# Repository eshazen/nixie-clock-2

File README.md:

# nixie-clock-2
Simple nixie clock based on ATMega861 microcontroller

<table>
  <tr>
    <td width=50%>
    <td>
</table>

```hardware/DriverBoard```

ExpressPCB layout for MCU/Driver board with ATTiny861A driving 4 IN-2B nixies.

```hardware/nixie_socket```

KiCAD design for a two-digit nixie mounting/breakout board

```software/clock```

C code for ATTiny861A to drive the clock display

```software/ESP8266```

Very simple NTP client to get the time via WiFi and send to the ATTiny

## Plans

Thinking of building one for the Kitchen.  Instead of ESP8622, thinking
of one of many DS3231 I2C RTC modules.  This could use the header wires
now used for the ESP.

For power, Triad FD4-10 has a dual 115V primary and 10VCT secondary.
Use a full-wave rectifier or bridge plus 7805 for 5V and the second primary
to generate the HV.  Also need a fuse/holder.

## Notes

On power-up/reboot, the ESP module transmits a blast of serial stuff
at a high bit rate.  This crashes the AVR code.  There's a 30 sec
timer which runs before enabling serial, but apparently the power-up
reset of the ESP sometimes fails.  So for now a reliable
power-up procedure:

* Apply AC power
* Press the reset button on the ESP fairly promptly

Then after 30s timeout things should come up OK.  I'd try to fix
this but can't easily locate my programming adapter for the AVR.

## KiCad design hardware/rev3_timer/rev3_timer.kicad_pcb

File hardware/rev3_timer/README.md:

# Rev 3 Timer

This is another try at the "Nixie kitchen timer" originally conceived
in about 2000.  The first rev PCB (ExpressPCB mini board) I used for a
clock in my office; the 2nd rev for another clock with a separate
display board (elsewhere in this repo).

Now planning a new, integrated board with 4 IN-12A/B Nixies, ATMega
328 (168, 88) and the following UI features:

* 4 digit nixie display for primary timer (00:00 to 59:59)
* Multiple simultaneous timers with distinctive sounds
* Water/splash proof case with waterproof buttons

Optional features

* RTC for time display
* Auxiliary LCD display 

## Status

**2023-03-07**

Combo PCB layout done which can be sheared in the middle into control
and display sections.  RTC and aux LCD not included.  Note that we
have a working RTC on the scope clock board so that could be added.

Looking at 3D builds.  See 3D directory.

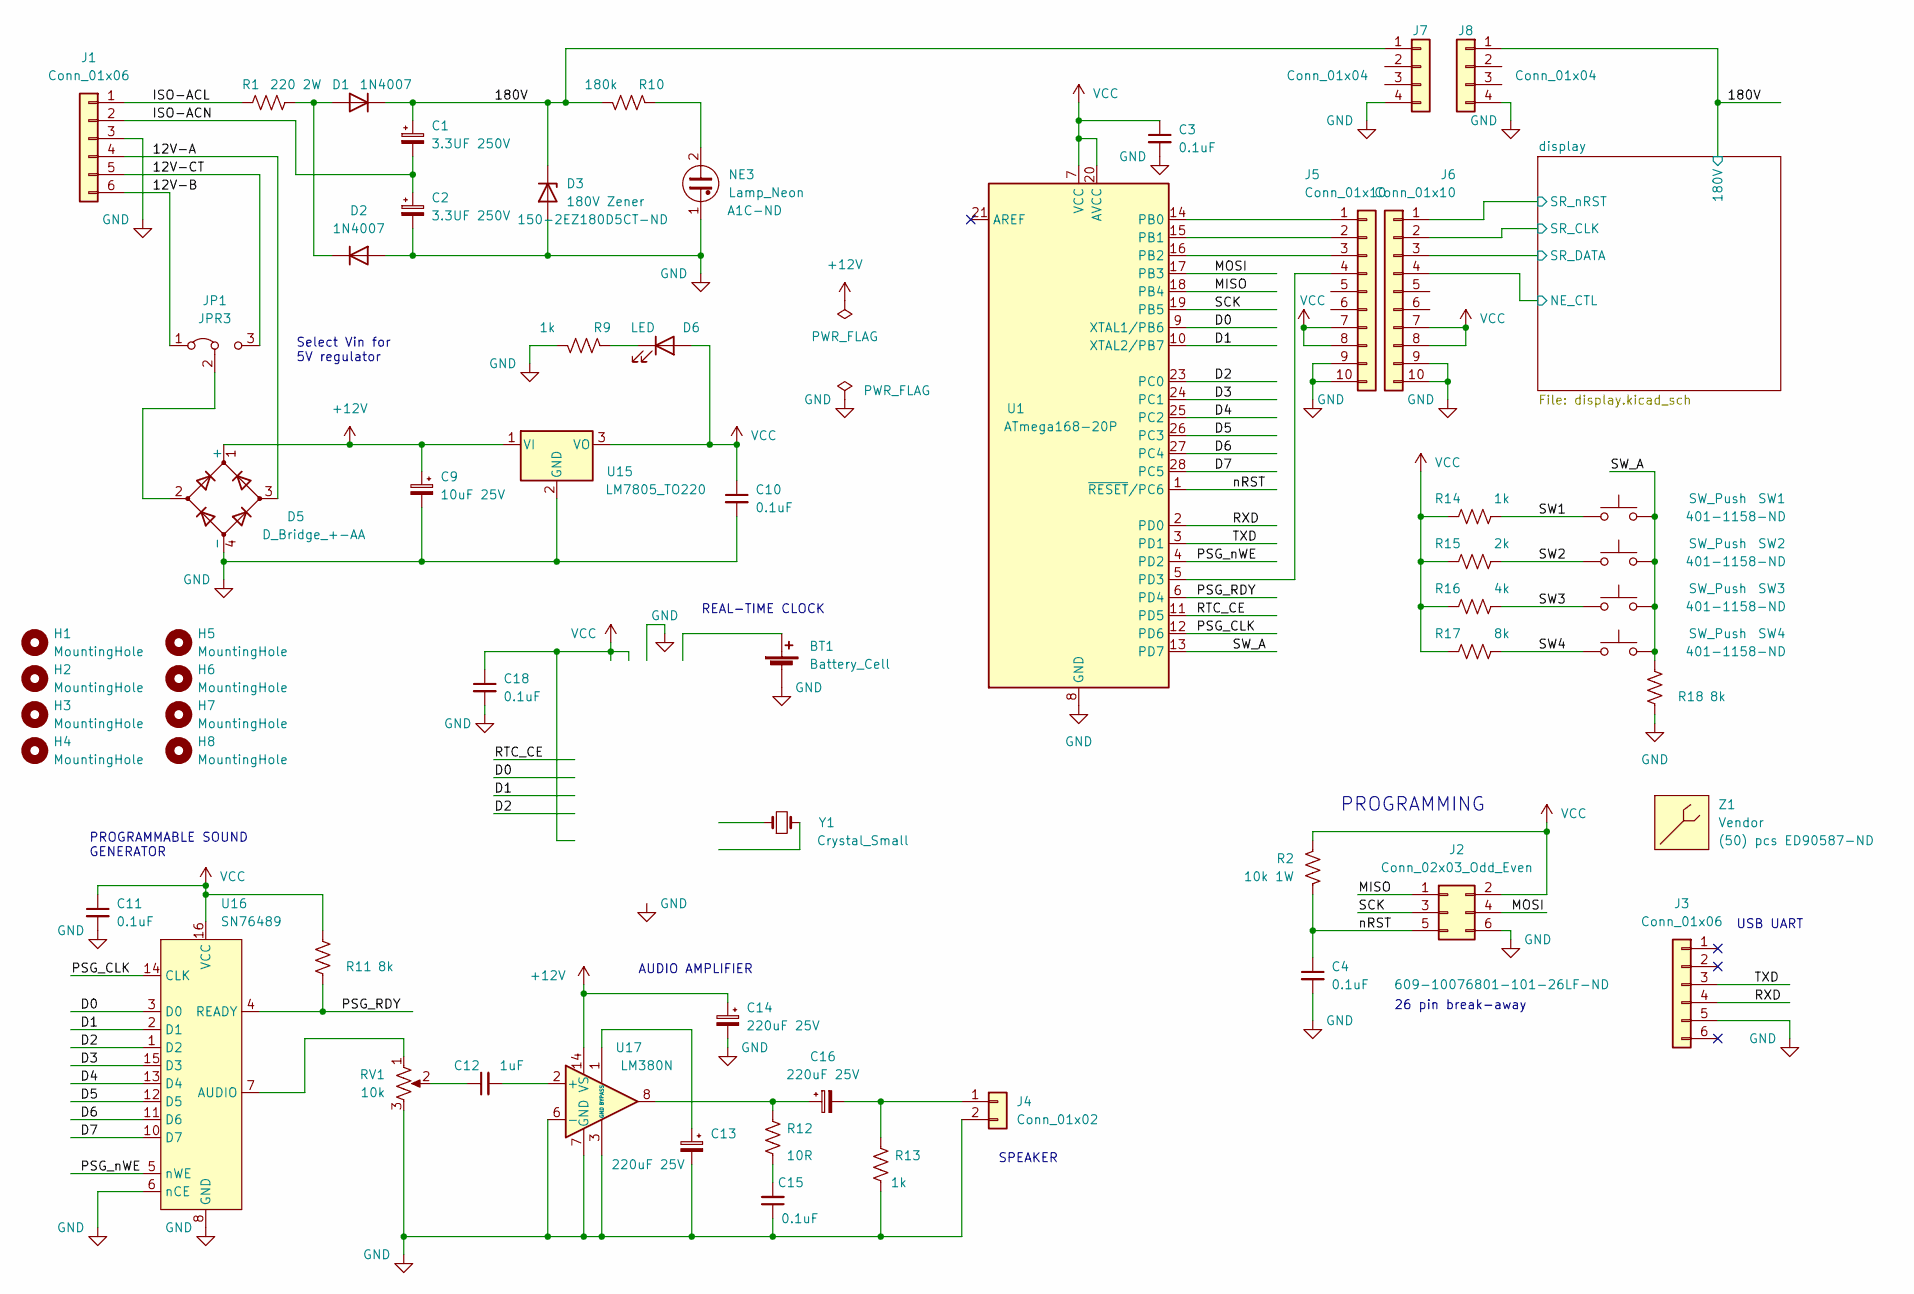
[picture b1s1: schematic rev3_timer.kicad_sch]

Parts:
BT1: Battery_Cell
C1, C2: 3.3UF 250V; CP_Radial_D8.0mm_P5.00mm
C3, C4, C10, C11, C15, C18: 0.1uF; C_Disc_D3.0mm_W1.6mm_P2.50mm
C9: 10uF 25V; CP_Radial_D5.0mm_P2.00mm
C12: 1uF; C_Rect_L7.2mm_W2.5mm_P5.00mm_FKS2_FKP2_MKS2_MKP2
C13, C14, C16: 220uF 25V; CP_Radial_D6.3mm_P2.50mm
D1, D2: 1N4007; D_DO-41_SOD81_P10.16mm_Horizontal
D3: 180V Zener; D_DO-41_SOD81_P10.16mm_Horizontal
D5: D_Bridge_+-AA; Diode_Bridge_Vishay_KBPM
D6: LED; LED_D3.0mm
H1, H2, H3, H4, H5, H6, H7, H8: MountingHole; MountingHole_4.3mm_M4_Pad
J1, J3: Conn_01x06; PinHeader_1x06_P2.54mm_Vertical
J2: Conn_02x03_Odd_Even; PinHeader_2x03_P2.54mm_Vertical
J4: Conn_01x02; PinHeader_1x02_P2.54mm_Vertical
J5, J6: Conn_01x10; PinHeader_2x05_P2.54mm_Vertical
J7, J8: Conn_01x04; PinHeader_1x04_P2.54mm_Vertical
JP1: JPR3; PinHeader_1x03_P2.54mm_Vertical
NE3: Lamp_Neon; PinHeader_1x02_P2.54mm_Vertical
R1: 220 2W; R_Axial_DIN0309_L9.0mm_D3.2mm_P15.24mm_Horizontal
R2: 10k 1W; R_Axial_DIN0207_L6.3mm_D2.5mm_P10.16mm_Horizontal
R9, R13, R14: 1k; R_Axial_DIN0207_L6.3mm_D2.5mm_P10.16mm_Horizontal
R10: 180k; R_Axial_DIN0207_L6.3mm_D2.5mm_P10.16mm_Horizontal
R11, R17, R18: 8k; R_Axial_DIN0207_L6.3mm_D2.5mm_P10.16mm_Horizontal
R12: 10R; R_Axial_DIN0207_L6.3mm_D2.5mm_P10.16mm_Horizontal
R15: 2k; R_Axial_DIN0207_L6.3mm_D2.5mm_P10.16mm_Horizontal
R16: 4k; R_Axial_DIN0207_L6.3mm_D2.5mm_P10.16mm_Horizontal
RV1: 10k; Potentiometer_ACP_CA6-H2,5_Horizontal
SW1, SW2, SW3, SW4: SW_Push; ck-switch-k12c
U1: ATmega168-20P; DIP-28_W7.62mm
U15: LM7805_TO220; TO-220-3_Vertical
U16: SN76489; DIP-16_W7.62mm_Socket
U17: LM380N; DIP-14_W7.62mm
Y1: Crystal_Small; Crystal_C26-LF_D2.1mm_L6.5mm_Horizontal
Z1: BOM_Item

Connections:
+12V: C9.1, C14.1, D5.1 (+), U15.1 (VI), U17.14 (VS)
/180V: C1.1, D1.1 (K), D3.1 (K), J7.1, J8.1, R10.1; also elsewhere on the board
/D0: U1.9 (XTAL1/PB6), U16.3 (D0); also elsewhere on the board
/D1: U1.10 (XTAL2/PB7), U16.2 (D1); also elsewhere on the board
/D2: U1.23 (PC0), U16.1 (D2); also elsewhere on the board
/D3: U1.24 (PC1), U16.15 (D3)
/D4: U1.25 (PC2), U16.13 (D4)
/D5: U1.26 (PC3), U16.12 (D5)
/D6: U1.27 (PC4), U16.11 (D6)
/D7: U1.28 (PC5), U16.10 (D7)
/ISO-ACL: J1.1, R1.1
/ISO-ACN: C1.2, C2.1, J1.2
/MISO: J2.1, U1.18 (PB4)
/MOSI: J2.4, U1.17 (PB3)
/PSG_CLK: U1.12 (PD6), U16.14 (CLK)
/PSG_RDY: R11.1, U1.6 (PD4), U16.4 (READY)
/PSG_nWE: U1.4 (PD2), U16.5 (nWE)
/RTC_CE: U1.11 (PD5); also elsewhere on the board
/RXD: J3.4, U1.2 (PD0)
/SCK: J2.3, U1.19 (PB5)
/SW1: R14.2, SW1.1
/SW2: R15.2, SW2.1
/SW3: R16.2, SW3.1
/SW4: R17.2, SW4.1
/SW_A: R18.2, SW1.2, SW2.2, SW3.2, SW4.2, U1.13 (PD7)
/TXD: J3.3, U1.3 (PD1)
/display/NE_CTL: J6.4; also elsewhere on the board
/display/SR_CLK: J6.2; also elsewhere on the board
/display/SR_DATA: J6.3; also elsewhere on the board
/display/SR_nRST: J6.1; also elsewhere on the board
/nRST: C4.1, J2.5, R2.1, U1.1 (~RESET/PC6)
unnamed: C12.1, RV1.2
unnamed: C12.2, U17.2 (+)
unnamed: C13.1, U17.1 (BYPASS)
unnamed: C15.2, R12.1
unnamed: C16.1, R12.2, U17.8
unnamed: C16.2, J4.1, R13.2
unnamed: D1.2 (A), D2.1 (K), R1.2
unnamed: D5.2, JP1.2 (C)
unnamed: D6.1 (K), R9.2
unnamed: J5.1, U1.14 (PB0)
unnamed: J5.2, U1.15 (PB1)
unnamed: J5.3, U1.16 (PB2)
unnamed: J5.4, U1.5 (PD3)
unnamed: NE3.2, R10.2
unnamed: RV1.1, U16.7 (AUDIO)
unnamed 135: Y1.1; also elsewhere on the board
unnamed 136: Y1.2; also elsewhere on the board
VCC: C3.1, C10.1, C11.1, C18.1, D6.2 (A), J2.2, J5.7, J5.8, J6.7, J6.8, R2.2, R11.2, R14.1, R15.1, R16.1, R17.1, U1.7 (VCC), U1.20 (AVCC), U15.3 (VO), U16.16 (VCC); also elsewhere on the board

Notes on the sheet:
AUDIO AMPLIFIER
USB UART
Select Vin for 5V regulator
26 pin break-away
PROGRAMMING
PROGRAMMABLE SOUND GENERATOR
REAL-TIME CLOCK
SPEAKER

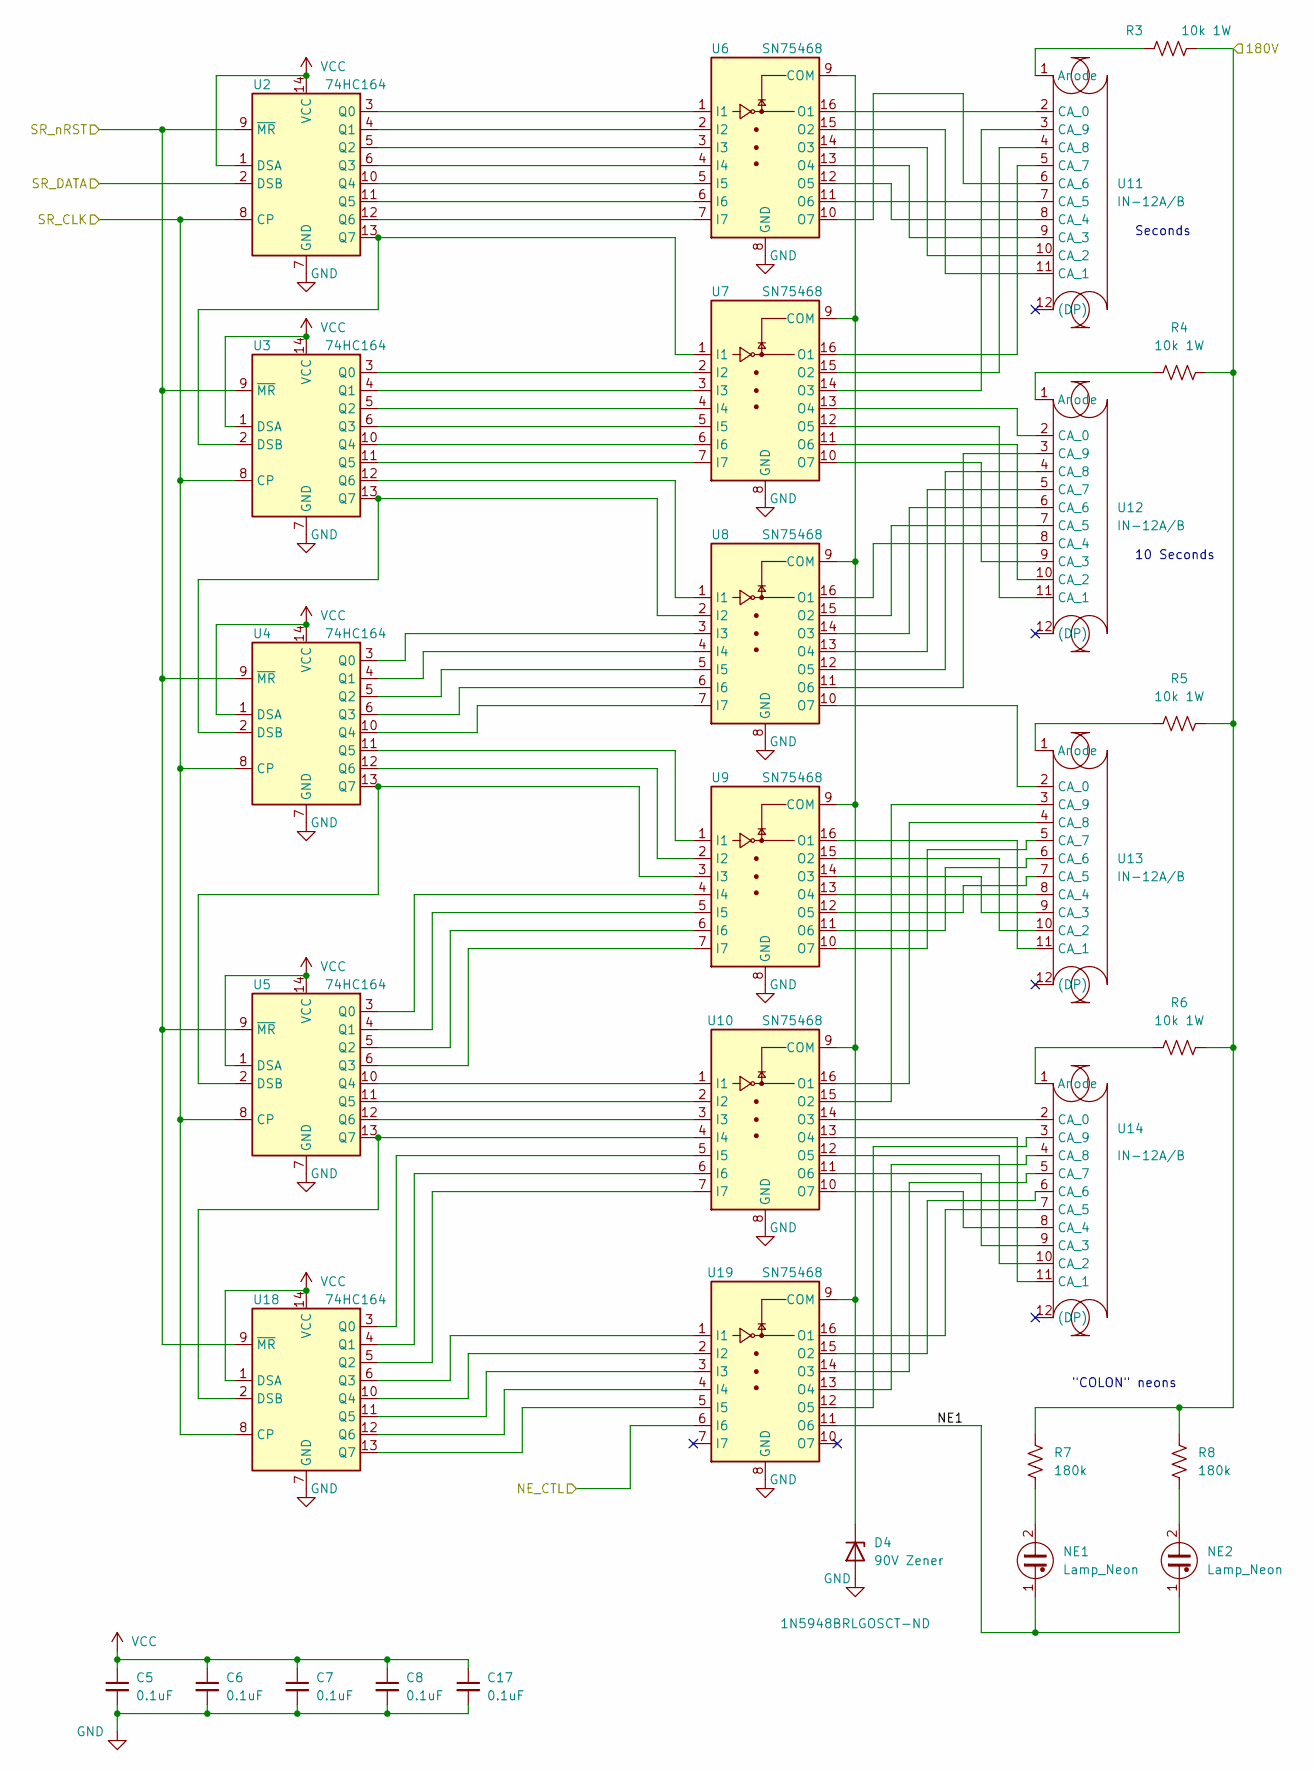
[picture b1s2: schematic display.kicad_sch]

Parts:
C5, C6, C7, C8, C17: 0.1uF; C_Disc_D3.0mm_W1.6mm_P2.50mm
D4: 90V Zener; D_DO-41_SOD81_P10.16mm_Horizontal
NE1, NE2: Lamp_Neon; PinHeader_1x02_P2.54mm_Vertical
R3, R4, R5, R6: 10k 1W; R_Axial_DIN0414_L11.9mm_D4.5mm_P20.32mm_Horizontal
R7, R8: 180k; R_Axial_DIN0207_L6.3mm_D2.5mm_P10.16mm_Horizontal
U2, U3, U4, U5, U18: 74HC164; DIP-14_W7.62mm_Socket
U6, U7, U8, U9, U10, U19: SN75468; DIP-16_W7.62mm_Socket
U11, U12, U13, U14: IN-12A/B; Nixie-8422-14pin

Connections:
/180V: R3.2, R4.2, R5.2, R6.2, R7.2, R8.2; also elsewhere on the board
/display/NE1: NE1.1, NE2.1, U19.11 (O6)
/display/NE_CTL: U19.6 (I6); also elsewhere on the board
/display/SR_CLK: U2.8 (CP), U3.8 (CP), U4.8 (CP), U5.8 (CP), U18.8 (CP); also elsewhere on the board
/display/SR_DATA: U2.2 (DSB); also elsewhere on the board
/display/SR_nRST: U2.9 (~MR), U3.9 (~MR), U4.9 (~MR), U5.9 (~MR), U18.9 (~MR); also elsewhere on the board
unnamed: D4.1 (K), U6.9 (COM), U7.9 (COM), U8.9 (COM), U9.9 (COM), U10.9 (COM), U19.9 (COM)
unnamed: NE1.2, R7.1
unnamed: NE2.2, R8.1
unnamed: R3.1, U11.1 (Anode)
unnamed: R4.1, U12.1 (Anode)
unnamed: R5.1, U13.1 (Anode)
unnamed: R6.1, U14.1 (Anode)
unnamed: U2.3 (Q0), U6.1 (I1)
unnamed: U2.4 (Q1), U6.2 (I2)
unnamed: U2.5 (Q2), U6.3 (I3)
unnamed: U2.6 (Q3), U6.4 (I4)
unnamed: U2.10 (Q4), U6.5 (I5)
unnamed: U2.11 (Q5), U6.6 (I6)
unnamed: U2.12 (Q6), U6.7 (I7)
unnamed: U2.13 (Q7), U3.2 (DSB), U7.1 (I1)
unnamed: U3.3 (Q0), U7.2 (I2)
unnamed: U3.4 (Q1), U7.3 (I3)
unnamed: U3.5 (Q2), U7.4 (I4)
unnamed: U3.6 (Q3), U7.5 (I5)
unnamed: U3.10 (Q4), U7.6 (I6)
unnamed: U3.11 (Q5), U7.7 (I7)
unnamed: U3.12 (Q6), U8.1 (I1)
unnamed: U3.13 (Q7), U4.2 (DSB), U8.2 (I2)
unnamed: U4.3 (Q0), U8.3 (I3)
unnamed: U4.4 (Q1), U8.4 (I4)
unnamed: U4.5 (Q2), U8.5 (I5)
unnamed: U4.6 (Q3), U8.6 (I6)
unnamed: U4.10 (Q4), U8.7 (I7)
unnamed: U4.11 (Q5), U9.1 (I1)
unnamed: U4.12 (Q6), U9.2 (I2)
unnamed: U4.13 (Q7), U5.2 (DSB), U9.3 (I3)
unnamed: U5.3 (Q0), U9.4 (I4)
unnamed: U5.4 (Q1), U9.5 (I5)
unnamed: U5.5 (Q2), U9.6 (I6)
unnamed: U5.6 (Q3), U9.7 (I7)
unnamed: U5.10 (Q4), U10.1 (I1)
unnamed: U5.11 (Q5), U10.2 (I2)
unnamed: U5.12 (Q6), U10.3 (I3)
unnamed: U5.13 (Q7), U10.4 (I4), U18.2 (DSB)
unnamed: U10.5 (I5), U18.3 (Q0)
unnamed: U10.6 (I6), U18.4 (Q1)
unnamed: U10.7 (I7), U18.5 (Q2)
unnamed: U10.10 (O7), U14.8 (CA_4)
unnamed: U10.11 (O6), U14.9 (CA_3)
unnamed: U10.12 (O5), U14.10 (CA_2)
unnamed: U10.13 (O4), U14.11 (CA_1)
unnamed: U10.14 (O3), U14.2 (CA_0)
unnamed: U10.15 (O2), U13.3 (CA_9)
unnamed: U10.16 (O1), U13.4 (CA_8)
unnamed: U6.16 (O1), U11.2 (CA_0)
unnamed: U7.14 (O3), U11.3 (CA_9)
unnamed: U7.15 (O2), U11.4 (CA_8)
unnamed: U7.16 (O1), U11.5 (CA_7)
unnamed: U6.10 (O7), U11.6 (CA_6)
unnamed: U6.11 (O6), U11.7 (CA_5)
unnamed: U6.12 (O5), U11.8 (CA_4)
unnamed: U6.13 (O4), U11.9 (CA_3)
unnamed: U6.14 (O3), U11.10 (CA_2)
unnamed: U6.15 (O2), U11.11 (CA_1)
unnamed: U7.13 (O4), U12.2 (CA_0)
unnamed: U8.11 (O6), U12.3 (CA_9)
unnamed: U8.12 (O5), U12.4 (CA_8)
unnamed: U8.13 (O4), U12.5 (CA_7)
unnamed: U8.14 (O3), U12.6 (CA_6)
unnamed: U8.15 (O2), U12.7 (CA_5)
unnamed: U8.16 (O1), U12.8 (CA_4)
unnamed: U7.10 (O7), U12.9 (CA_3)
unnamed: U7.11 (O6), U12.10 (CA_2)
unnamed: U7.12 (O5), U12.11 (CA_1)
unnamed: U8.10 (O7), U13.2 (CA_0)
unnamed: U9.10 (O7), U13.5 (CA_7)
unnamed: U9.11 (O6), U13.6 (CA_6)
unnamed: U9.12 (O5), U13.7 (CA_5)
unnamed: U9.13 (O4), U13.8 (CA_4)
unnamed: U9.14 (O3), U13.9 (CA_3)
unnamed: U9.15 (O2), U13.10 (CA_2)
unnamed: U9.16 (O1), U13.11 (CA_1)
unnamed: U14.3 (CA_9), U19.12 (O5)
unnamed: U14.4 (CA_8), U19.13 (O4)
unnamed: U14.5 (CA_7), U19.14 (O3)
unnamed: U14.6 (CA_6), U19.15 (O2)
unnamed: U14.7 (CA_5), U19.16 (O1)
unnamed: U18.6 (Q3), U19.1 (I1)
unnamed: U18.10 (Q4), U19.2 (I2)
unnamed: U18.11 (Q5), U19.3 (I3)
unnamed: U18.12 (Q6), U19.4 (I4)
unnamed: U18.13 (Q7), U19.5 (I5)
VCC: C5.1, C6.1, C7.1, C8.1, C17.1, U2.1 (DSA), U2.14 (VCC), U3.1 (DSA), U3.14 (VCC), U4.1 (DSA), U4.14 (VCC), U5.1 (DSA), U5.14 (VCC), U18.1 (DSA), U18.14 (VCC); also elsewhere on the board

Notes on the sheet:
"COLON" neons
Seconds
10 Seconds

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
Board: 2 copper layers, 88 parts (0 on the bottom side), 141 nets, no tracks yet.

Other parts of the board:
U20: DS1306; DIP-16_W7.62mm_Socket

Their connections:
/D0: U20.11 (SCLK); also elsewhere on the board
/D1: U20.12 (SDI); also elsewhere on the board
/D2: U20.13 (SDO); also elsewhere on the board
/RTC_CE: U20.10 (CE); also elsewhere on the board
unnamed 135: U20.3 (X1); also elsewhere on the board
unnamed 136: U20.4 (X2); also elsewhere on the board
VCC: U20.9 (SERMODE), U20.14 (VCCIF), U20.16 (VCC); also elsewhere on the board

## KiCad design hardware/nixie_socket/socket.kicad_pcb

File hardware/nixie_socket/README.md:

This is a design for a simple nixie breakout board for two IN-2B or
B-5991 nixies.  I used DB-25 type female pins as individual sockets
for the nixies.

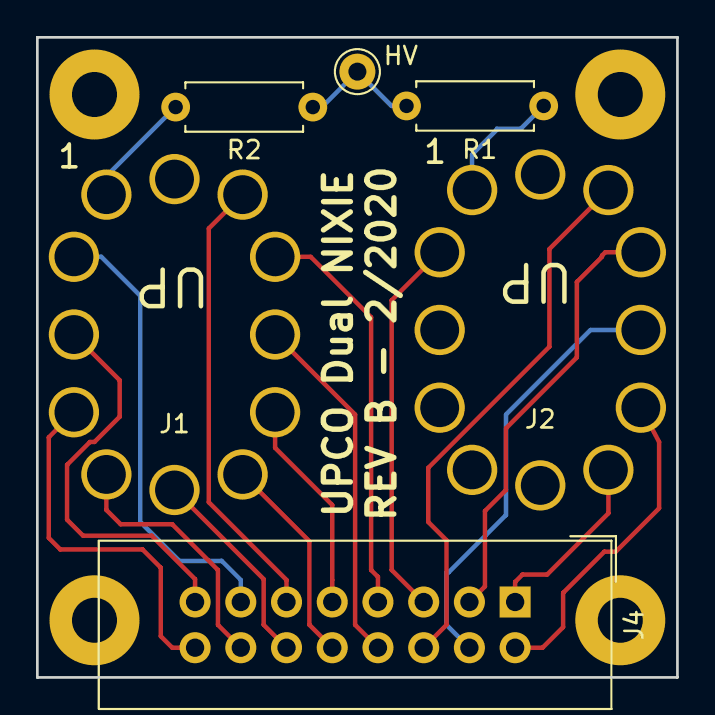
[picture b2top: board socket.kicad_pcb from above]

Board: 2 copper layers, 35.6 x 35.6 mm, 7 parts (0 on the bottom side), 19 nets.

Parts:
J1, J2: Nixie; Nixie-8422-14pin
J3: HV; Pin_D1.0mm_L10.0mm
J4: Conn_02x08_Odd_Even; IDC-Header_2x08_P2.54mm_Vertical
R1, R2: R_US; R_Axial_DIN0207_L6.3mm_D2.5mm_P7.62mm_Horizontal
x1: MountingHole_2.5mm_Pad

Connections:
unnamed: J1.1, R2.2
unnamed: J1.2, J4.13
unnamed: J1.3, J4.15
unnamed: J1.4, J4.16
unnamed: J1.5, J4.14
unnamed: J1.6, J4.12
unnamed: J1.7, J4.10
unnamed: J1.8, J4.9
unnamed: J1.9, J4.8
unnamed: J1.10, J4.7
unnamed: J1.11, J4.11
unnamed: J2.1, R1.2
unnamed: J2.2, J4.5
unnamed: J2.7, J4.1
unnamed: J2.8, J4.2
unnamed: J2.9, J4.4
unnamed: J2.10, J4.3
unnamed: J2.11, J4.6
unnamed: J3.1, R1.1, R2.1

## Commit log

2020-06-08 Uploading hardware design
2020-06-08 Add socket PCB
2020-06-08 adding clock firmware
2020-06-08 Add ESP8266 client
2020-06-09 Add layout png
2020-06-09 Add box sketch
2020-06-27 Clock firmware updates: disable on-board time update as it was fighting with the NTP time updates. Found that EPS8266 boot-up emits a high-baud blurp which would crash the AVR, so added a 30s start-u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
2020-06-28 Add block diagram
2020-06-28 add photo
2020-06-28 add pics
2022-12-03 cleanup
2022-12-04 readme
2022-12-04 add ESP holder draft
2022-12-08 Holder seems to fit now
2023-02-06 socket board and new timer
2023-02-06 .gitignore is now working
2023-02-07 working on placement
2023-02-18 working on two-board design
2023-03-06 playing with placement
2023-03-07 working on 3D
2023-03-08 add RTC, rearrange placement
2023-03-16 Update client to handle DST
